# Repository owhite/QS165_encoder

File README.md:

# QS165 motor magentic encoder with hall output

One scope probe (red) connected to "W" output of board, and another probe (yellow) is tied to the phase output of the QS165. The QS165 is turned by hand as described here: 

[LINK](https://github.com/badgineer/MP2-ESC/blob/main/docs/MOTOR_PARAM.md).

## An encoder retrofit for the QS165 motor [[See this link](AS5048_extburn/README.md)].

This encoder is designed as a drop in replacement to the QS165 motor and uses an AS5047 to generates UVW output. In order for this to work you'll need to program the AS5047 with an external CPU. So basically this is **unnecessarily expensive requiring purchase of a custum PCB and a teensy to program the board. It is unnecessarily complicated in that it requires a custom programmer dongle, common bench testing equipment, assembling a board, and knowledge of programming**. 

On the other hand I'm not aware of a lot of alternatives. 

### **Acknowledgement:**
* [CircularBuffer](https://github.com/CircularBuffer/AS5047P) supplied code to burn the AS5047 non-volatile memory.
* [David Molony](https://github.com/davidmolony) kindly helped with some development of early boards. 

## Schematic

## To build board and test
* Order and construct [this kicad board](AS5047_extburn/README.md)
* Create the programming dongle shown below
* Select between 3.3V versus 5V operation with solder jumper
* Please note: using 5V on the 3.3V definitely kills the chip
* Connect up up the finished PCB on the bench or motor
* Confirm the initial outputs of the AS5047 with an oscilloscope

## Programming
The AS5047 uses one time progromming to change some of it's registers permanantly. Note that programming definitely means you get **one time** to program the chip -- so be careful. 

As [CircularBuffer](https://github.com/CircularBuffer/AS5047P) points out, that code will probably work on a number of platforms. This works for me:

* Review [main.ino](https://github.com/owhite/QS165_encoder/tree/main/FIRMWARE/encoder/src/main.ino) carefully to understand how variables are sent to the AS5047 and the program flow
* Default variables for QS165 are set in main.ino using the lines:

```
  AS5047P_SetFieldInRegister(&encInstanceA, AS5047P_SETTINGS1, AS5047P_SETTINGS1_PWMON, 1);
  AS5047P_SetFieldInRegister(&encInstanceA, AS5047P_SETTINGS1, AS5047P_SETTINGS1_UVW_ABI, 1);
  AS5047P_SetFieldInRegister(&encInstanceA, AS5047P_SETTINGS2, AS5047P_SETTINGS2_UVWPP, 6);
```

Note: the QS165 has 7 polepairs, and according to the AS5047 docs you pass it a '6'. 

* Salt to taste if you have something else
* Load code on teensy board using the platformio environment to install [code](https://github.com/owhite/QS165_encoder/tree/main/FIRMWARE/encoder)
* Once programmed, connect teensy to encoder board using programming-dongle
* Start up a serial terminal
* While program is running, review the program is effectively communicating with the encoder board
* Confirm you like the actual output of the pins on encoder board
* Entering single characters into the serial input gets ready for the burn
* Typing anything besides "x" shows you serial input is working
* Enter "x" when youre ready to burn
* main.ino will report "no errors received, test if burn complete" if it worked
* Once it is programmed, youre done, and the AS5047 will not let you burn again.

## Programming hardware

An example of programming a earlier version of the encoder board with a teensy 3.6, ribbon cable and 6 pin connector. 

Pogo pins may be helpful for making quick connections to the board. 

## Shout out to my friends:
* Need a nice open source motor controller? Try the [MP2](https://github.com/badgineer/MP2-ESC). 
* Need some firmware to run on the motor controller? Try [MESC](https://github.com/davidmolony/MESC_Firmware). 
* A discussion of the QS165 on [endless-sphere](https://endless-sphere.com/forums/viewtopic.php?p=1748544).
* Two great sites for PCB and PCBA: [pcbway.com](https://www.pcbway.com/) and [jlcpcb.com](https://jlcpcb.com/).

## Final notes: some examples of other attempts to create an encoder
### **Attempt: AS5048 with line isolation [[LINK](AS5048_isolation/README.md)].**

Note: was not bad, just sort of complicated to use SPI with ESC.

### **Attempt: atmega328p to AS5048 [[LINK](AS5048_atmega328p/README.md)].**

Notes: Never really got this to work. 
* decoupling caps werent doing their job on original design which could be the cause;
* original xtal just didnt work;
* this may have resulted in serial writing bad characters;
* and programming problems. 

And, it's not clear the clock speed would ever be fast enough for SPI communications and reasonable output

PCB was set up for 5v. 

### **Attempt: AS5047 with on board CPU [[LINK](AS5047_atmega328p/README.md)].** 
This actually generated some reasonable output, but the downside it required the atmega to push SPI instructions to the AS5047.

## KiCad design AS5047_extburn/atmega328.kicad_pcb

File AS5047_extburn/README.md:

# An encoder retrofit for the QS165 motor.

Review this [README](../README.md) for more information.

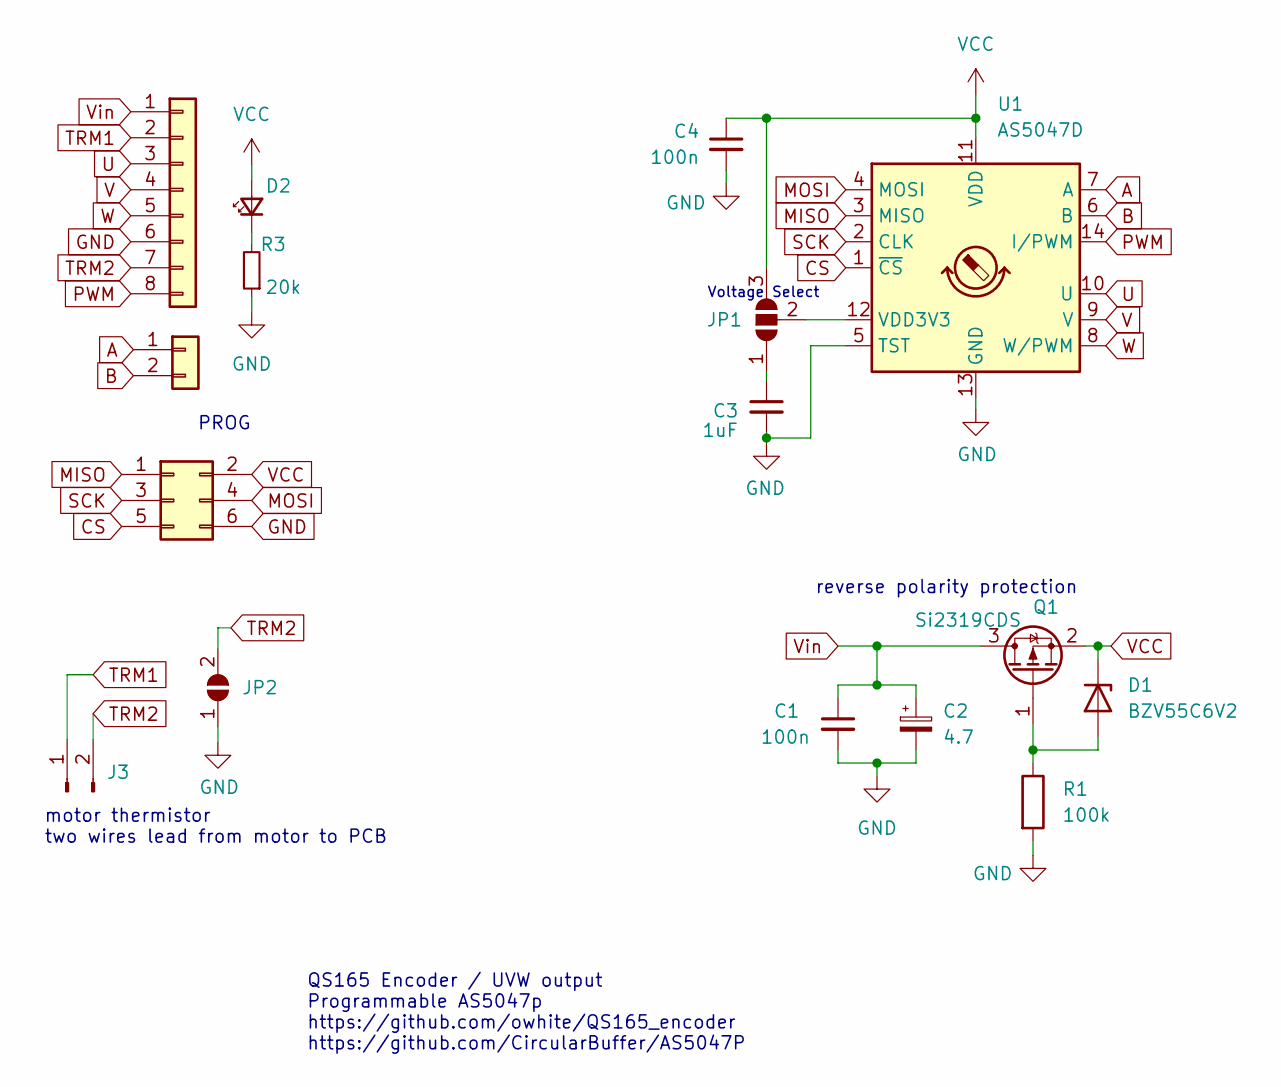
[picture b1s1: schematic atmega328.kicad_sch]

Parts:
C1, C4: 100n; C_0805_2012Metric
C2: 4.7; CP_EIA-3216-18_Kemet-A; LCSC C110055
C3: 1uF; C_0805_2012Metric
D1: BZV55C6V2; D_MiniMELF; LCSC C266263
D2: RED_LED; LED_0805_2012Metric
J1: Conn_01x02; PinHeader_1x02_P2.54mm_Vertical
J3: Conn_01x02_Male; PinHeader_1x02_P2.54mm_Vertical
J5: Conn_01x08; PinHeader_1x08_P2.54mm_Vertical
JP1: SolderJumper_3_Open; SolderJumper-3_P1.3mm_Open_RoundedPad1.0x1.5mm
JP2: SolderJumper_2_Open; SolderJumper-2_P1.3mm_Open_Pad1.0x1.5mm
PRG1: Conn_02x03_Top_Bottom; isp_6pin
Q1: Si2319CDS; SOT-23; LCSC C558254
R1: 100k; R_0805_2012Metric
R3: 20k; R_0805_2012Metric
U1: AS5047D; TSSOP-14_4.4x5mm_P0.65mm

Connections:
A: J1.1, U1.7 (A)
B: J1.2, U1.6 (B)
CS: PRG1.5, U1.1 (~CS)
GND: C1.2, C2.2, C3.2, C4.2, J5.6, JP2.1 (A), PRG1.6, R1.2, R3.1, U1.5 (TST), U1.13 (GND)
MISO: PRG1.1, U1.3 (MISO)
MOSI: PRG1.4, U1.4 (MOSI)
unnamed: C3.1, JP1.1 (A)
unnamed: D1.2 (A), Q1.1 (G), R1.1
unnamed: D2.1 (K), R3.2
unnamed: JP1.2 (C), U1.12 (VDD3V3)
PWM: J5.8, U1.14 (I/PWM)
SCK: PRG1.3, U1.2 (CLK)
TRM1: J3.1, J5.2
TRM2: J3.2, J5.7, JP2.2 (B)
U: J5.3, U1.10 (U)
V: J5.4, U1.9 (V)
VCC: C4.1, D1.1 (K), D2.2 (A), JP1.3 (B), PRG1.2, Q1.2 (S), U1.11 (VDD)
Vin: C1.1, C2.1, J5.1, Q1.3 (D)
W: J5.5, U1.8 (W/PWM)

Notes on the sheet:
QS165 Encoder / UVW output Programmable AS5047p https://github.com/owhite/QS165_encoder https://github.com/CircularBuffer/AS5047P
motor thermistor two wires lead from motor to PCB
PROG
reverse polarity protection
Voltage Select

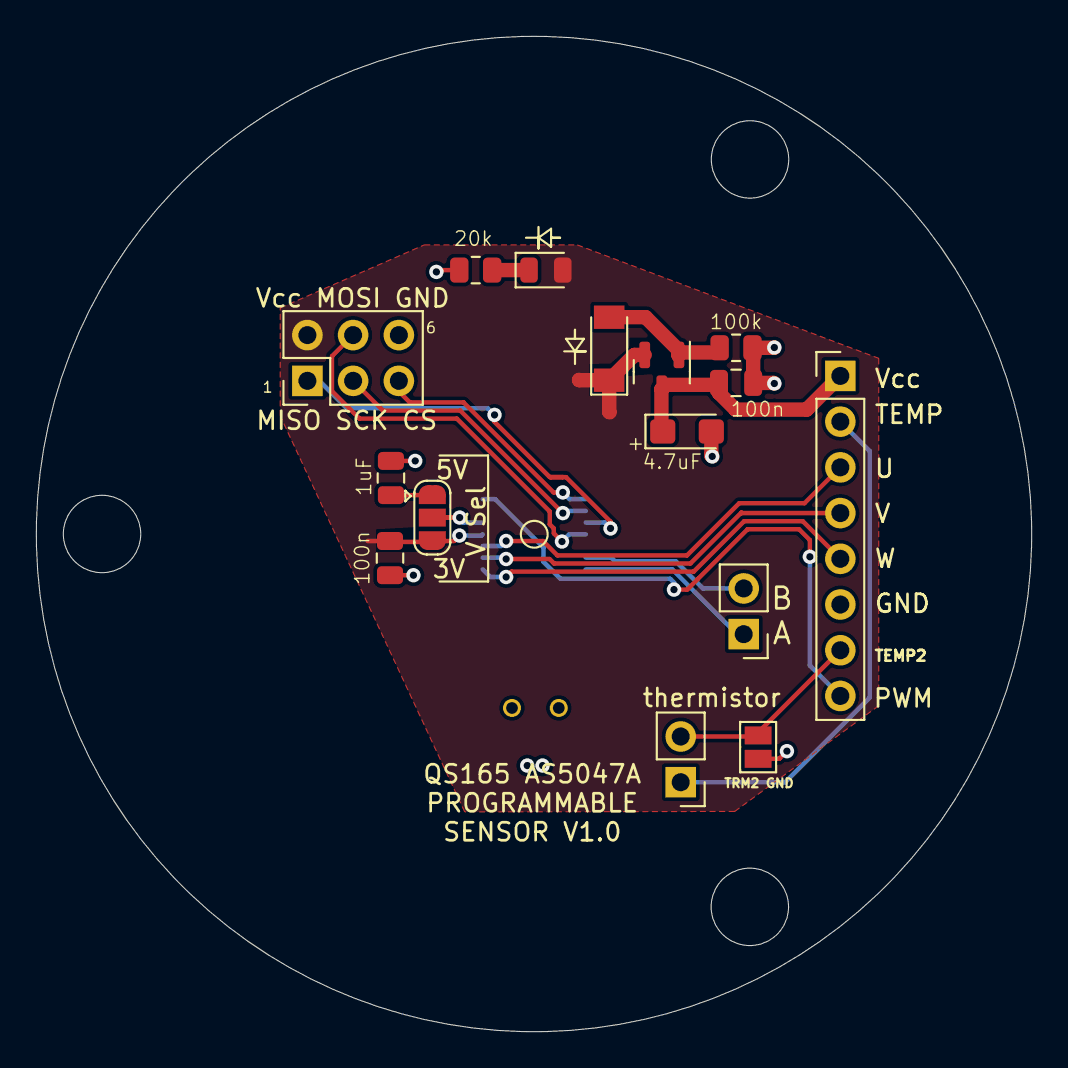
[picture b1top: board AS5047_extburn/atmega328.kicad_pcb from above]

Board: 2 copper layers, 55.3 x 55.3 mm, 16 parts (1 on the bottom side), 19 nets.

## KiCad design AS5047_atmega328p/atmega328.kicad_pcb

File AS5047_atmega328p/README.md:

# Native AS5047 hall output, driven by atmega328p

See the firmware directory to run the atmega.

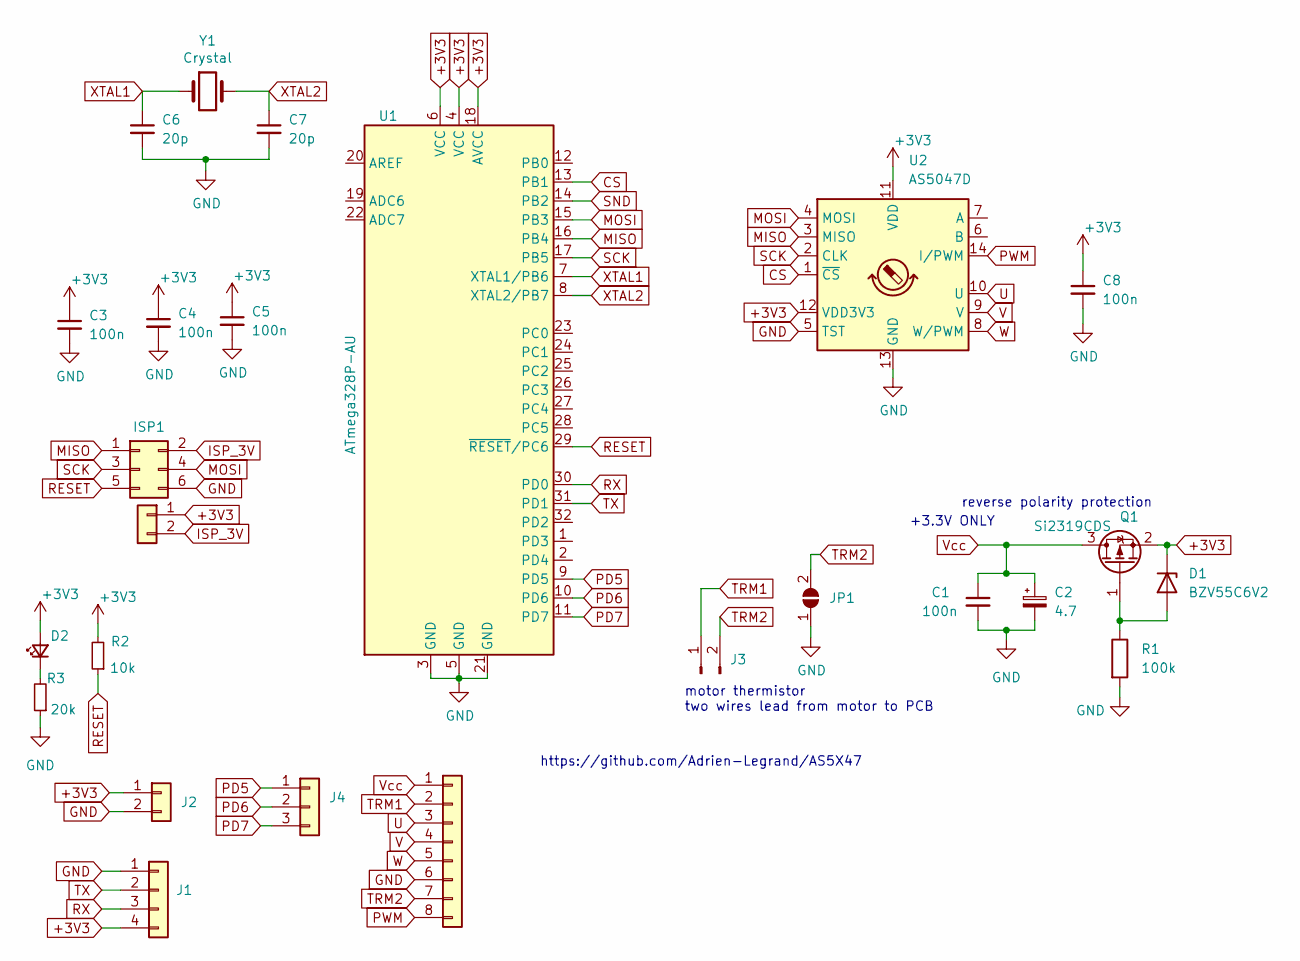
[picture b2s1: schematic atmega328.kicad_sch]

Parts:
C1: 100n; C_0603_1608Metric; LCSC C346191
C2: 4.7; CP_EIA-3216-18_Kemet-A; LCSC C110055
C3, C4, C5, C8: 100n; C_0402_1005Metric; LCSC C1525
C6, C7: 20p; C_0402_1005Metric; LCSC C76959
D1: BZV55C6V2; D_MiniMELF; LCSC C266263
D2: RED_LED; LED_0603_1608Metric; LCSC C90692
ISP1: Conn_02x03_Top_Bottom; isp_6pin
J1: Conn_01x04; PinHeader_1x04_P2.54mm_Vertical
J2: Conn_01x02; myPinHeader_1x02_P2.54mm_Vertical
J3: Conn_01x02_Male; PinHeader_1x02_P2.54mm_Vertical
J4: Conn_01x03; PinHeader_1x03_P2.54mm_Vertical
J5: Conn_01x08; PinHeader_1x08_P2.54mm_Vertical
J6: Conn_01x02; PinHeader_1x02_P2.54mm_Vertical
JP1: SolderJumper_2_Open; SolderJumper-2_P1.3mm_Open_Pad1.0x1.5mm
Q1: Si2319CDS; SOT-23; LCSC C558254
R1: 100k; R_0603_1608Metric; LCSC C14675
R2: 10k; R_0603_1608Metric; LCSC C98220
R3: 20k; R_0603_1608Metric; LCSC C365403
U1: ATmega328P-AU; TQFP-32_7x7mm_P0.8mm; LCSC C14877
U2: AS5047D; TSSOP-14_4.4x5mm_P0.65mm
Y1: Crystal; Crystal_SMD_5032-2Pin_5.0x3.2mm

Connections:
+3V3: C3.1, C4.1, C5.1, C8.1, D1.1 (K), D2.2 (A), J1.4, J2.1, J6.1, Q1.2 (S), R2.2, U1.4 (VCC), U1.6 (VCC), U1.18 (AVCC), U2.11 (VDD), U2.12 (VDD3V3)
CS: U1.13 (PB1), U2.1 (~CS)
GND: C1.2, C2.2, C3.2, C4.2, C5.2, C6.2, C7.2, C8.2, ISP1.6, J1.1, J2.2, J5.6, JP1.1 (A), R1.2, R3.1, U1.3 (GND), U1.5 (GND), U1.21 (GND), U2.5 (TST), U2.13 (GND)
ISP_3V: ISP1.2, J6.2
MISO: ISP1.1, U1.16 (PB4), U2.3 (MISO)
MOSI: ISP1.4, U1.15 (PB3), U2.4 (MOSI)
unnamed: D1.2 (A), Q1.1 (G), R1.1
unnamed: D2.1 (K), R3.2
PD5: J4.1, U1.9 (PD5)
PD6: J4.2, U1.10 (PD6)
PD7: J4.3, U1.11 (PD7)
PWM: J5.8, U2.14 (I/PWM)
RESET: ISP1.5, R2.1, U1.29 (~RESET/PC6)
RX: J1.3, U1.30 (PD0)
SCK: ISP1.3, U1.17 (PB5), U2.2 (CLK)
SND: U1.14 (PB2)
TRM1: J3.1, J5.2
TRM2: J3.2, J5.7, JP1.2 (B)
TX: J1.2, U1.31 (PD1)
U: J5.3, U2.10 (U)
V: J5.4, U2.9 (V)
Vcc: C1.1, C2.1, J5.1, Q1.3 (D)
W: J5.5, U2.8 (W/PWM)
XTAL1: C6.1, U1.7 (XTAL1/PB6), Y1.1
XTAL2: C7.1, U1.8 (XTAL2/PB7), Y1.2

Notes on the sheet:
+3.3V ONLY
motor thermistor two wires lead from motor to PCB
reverse polarity protection
https://github.com/Adrien-Legrand/AS5X47

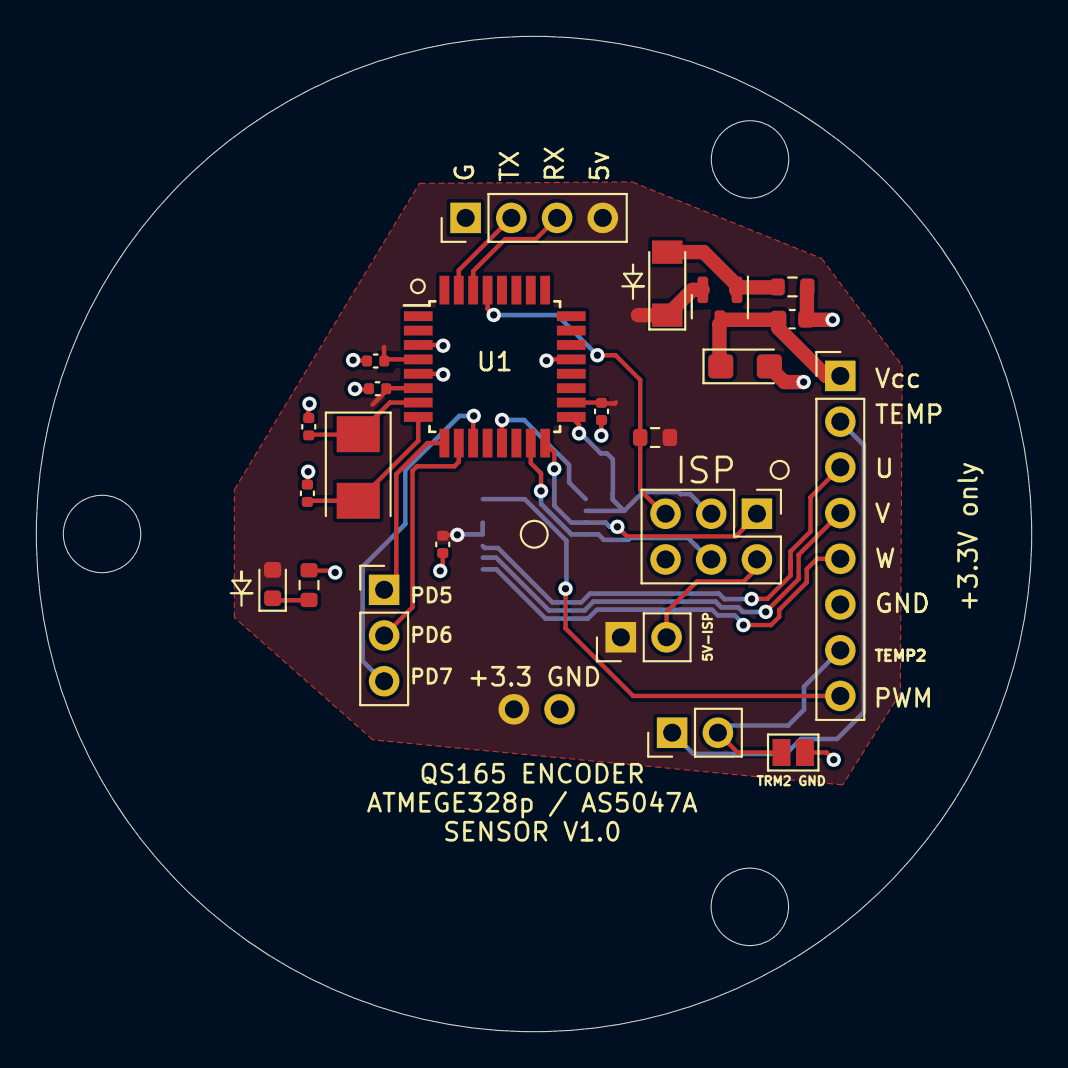
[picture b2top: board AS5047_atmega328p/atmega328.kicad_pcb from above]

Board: 2 copper layers, 55.3 x 55.3 mm, 25 parts (1 on the bottom side), 24 nets.

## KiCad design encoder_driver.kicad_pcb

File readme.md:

# QS165_encoder
QS165 encoder based on the TLE5012B encoder and galvanic isolators.

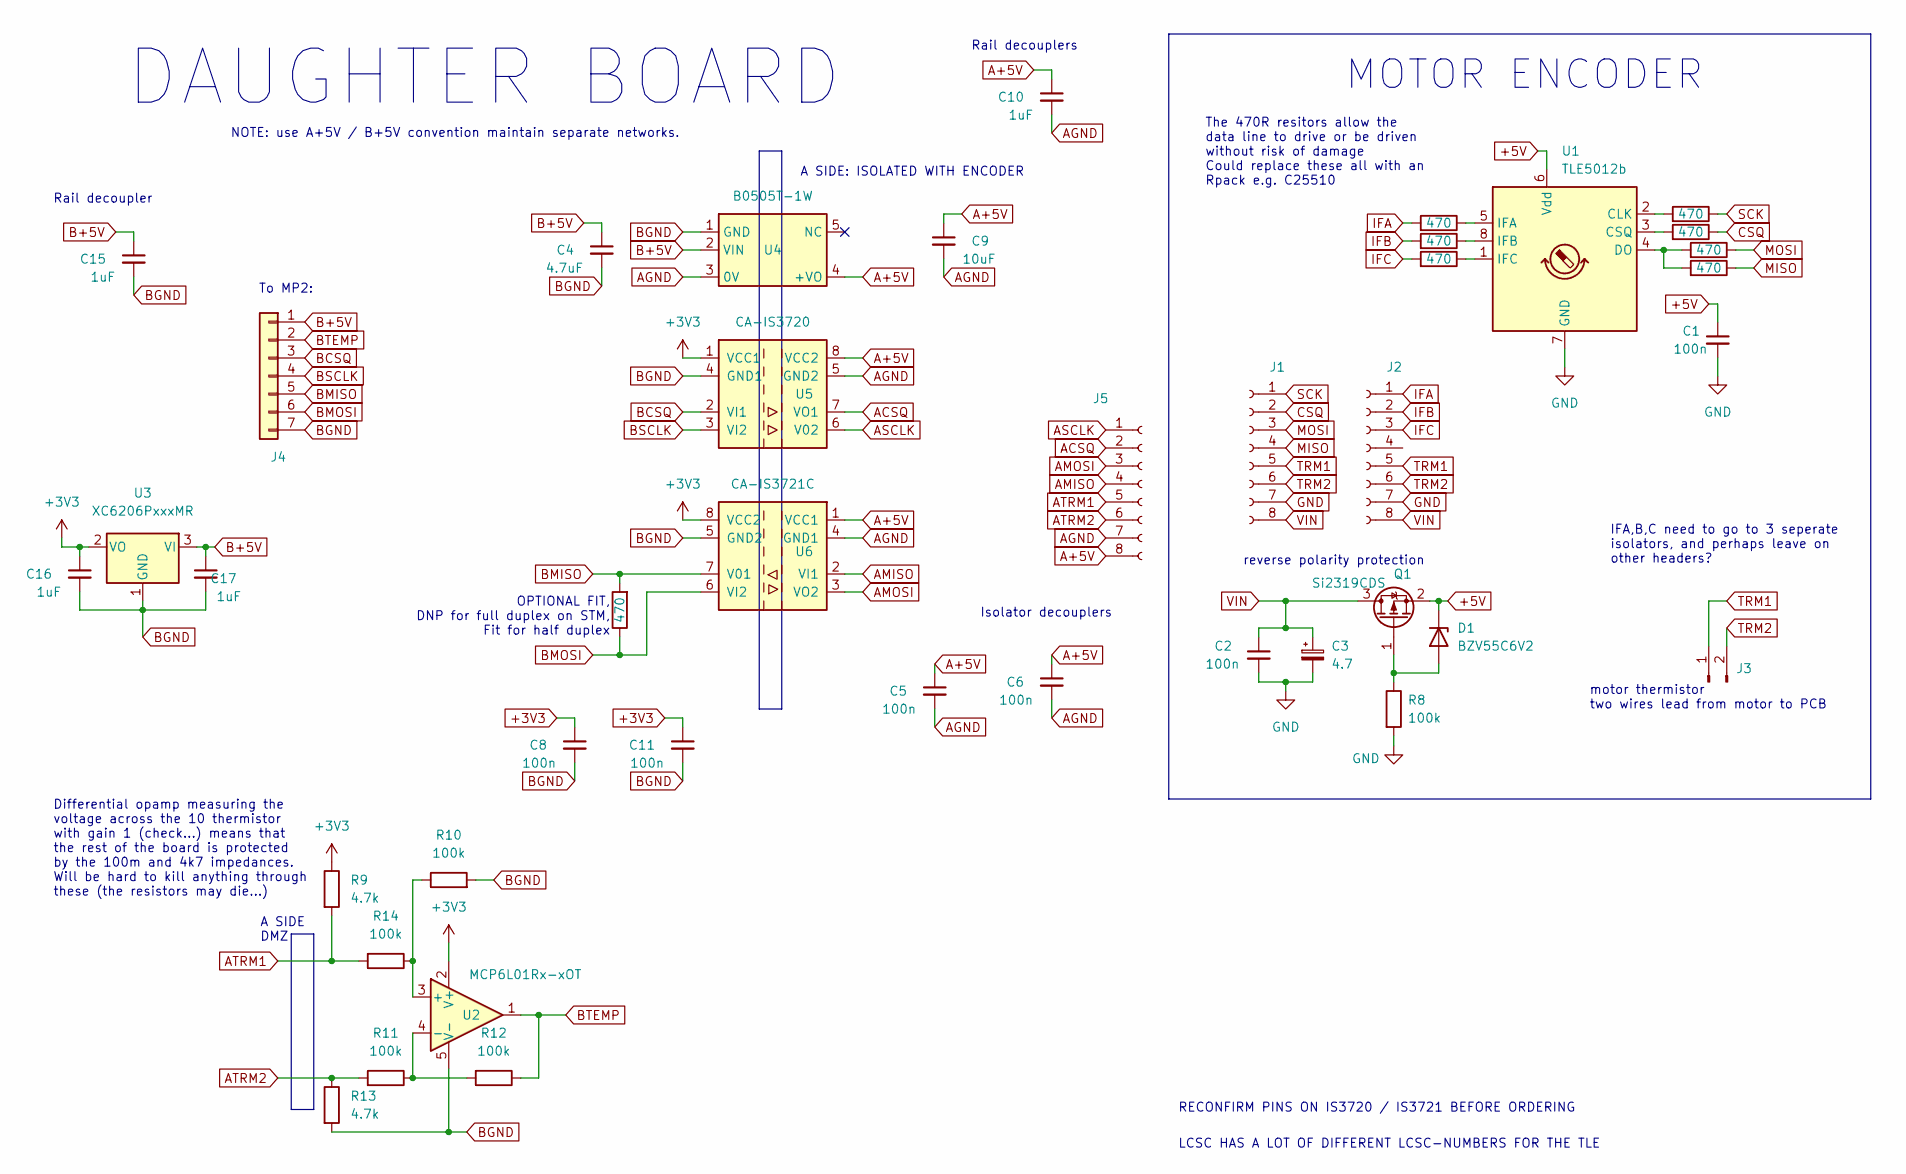
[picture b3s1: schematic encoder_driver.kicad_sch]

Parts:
C1, C2: 100n; C_0603_1608Metric; LCSC C14663
C3: 4.7; CP_EIA-3216-18_Kemet-A; LCSC C110055
C4: 4.7uF; C_0603_1608Metric; LCSC C15849
C5, C6, C8, C11: 100n; C_0402_1005Metric; LCSC C14663
C9: 10uF; C_0603_1608Metric; LCSC C15849
C10, C15, C16, C17: 1uF; C_0603_1608Metric; LCSC C15849
D1: BZV55C6V2; D_MiniMELF; LCSC C266263
J1, J2: Conn_01x08_Female; PinSocket_1x08_P2.54mm_Vertical
J3: Conn_01x02_Male; PinHeader_1x02_P2.54mm_Vertical
J4: Conn_01x07; PinSocket_1x07_P2.00mm_Vertical
J5: Conn_01x08_Female; PinHeader_1x08_P2.54mm_Vertical
Q1: Si2319CDS; SOT-23; LCSC C558254
R1, R2, R3, R4, R5, R6, R7, R15: 470; R_0603_1608Metric; LCSC C23179
R8: 100k; R_0603_1608Metric; LCSC C25803
R9, R13: 4.7k; R_0402_1005Metric; LCSC C23186
R10, R11, R12, R14: 100k; R_0402_1005Metric; LCSC C25803
U1: TLE5012b; my_Infineon_PG-DSO-8
U2: MCP6L01Rx-xOT; SOT-23-5; LCSC C693056
U3: XC6206PxxxMR; SOT-23; LCSC C5446
U4: B0505T-1W; PWRM-SMD_B0505XT-1WR2; LCSC C30338
U5: CA-IS3720; SOIC-8_3.9x4.9mm_P1.27mm; LCSC C428882
U6: CA-IS3721C; SOIC-8_3.9x4.9mm_P1.27mm; LCSC C5121216

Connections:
+3V3: C8.1, C11.1, C16.1, R9.1, U2.2 (V+), U3.2 (VO), U5.1 (VCC1), U6.8 (VCC2)
+5V: C1.1, D1.1 (K), Q1.2 (S), U1.6 (Vdd)
A+5V: C5.1, C6.1, C9.1, C10.1, J5.8, U4.4 (+VO), U5.8 (VCC2), U6.1 (VCC1)
ACSQ: J5.2, U5.7 (VO1)
AGND: C5.2, C6.2, C9.2, C10.2, J5.7, U4.3 (0V), U5.5 (GND2), U6.4 (GND1)
AMISO: J5.4, U6.2 (VI1)
AMOSI: J5.3, U6.3 (VO2)
ASCLK: J5.1, U5.6 (V02)
ATRM1: J5.5, R9.2, R14.2
ATRM2: J5.6, R11.2, R13.1
B+5V: C4.1, C15.1, C17.1, J4.1, U3.3 (VI), U4.2 (VIN)
BCSQ: J4.3, U5.2 (VI1)
BGND: C4.2, C8.2, C11.2, C15.2, C16.2, C17.2, J4.7, R10.2, R13.2, U2.5 (V-), U3.1 (GND), U4.1 (GND), U5.4 (GND1), U6.5 (GND2)
BMISO: J4.5, R15.2, U6.7 (V01)
BMOSI: J4.6, R15.1, U6.6 (VI2)
BSCLK: J4.4, U5.3 (VI2)
BTEMP: J4.2, R12.1, U2.1
CSQ: J1.2, R5.1
GND: C1.2, C2.2, C3.2, J1.7, J2.7, R8.2, U1.7 (GND)
IFA: J2.1, R1.2
IFB: J2.2, R2.2
IFC: J2.3, R3.2
MISO: J1.4, R7.1
MOSI: J1.3, R6.1
unnamed: D1.2 (A), Q1.1 (G), R8.1
unnamed: R1.1, U1.5 (IFA)
unnamed: R2.1, U1.8 (IFB)
unnamed: R3.1, U1.1 (IFC)
unnamed: R4.2, U1.2 (CLK)
unnamed: R5.2, U1.3 (CSQ)
unnamed: R6.2, R7.2, U1.4 (DO)
unnamed: R10.1, R14.1, U2.3 (+)
unnamed: R11.1, R12.2, U2.4 (-)
SCK: J1.1, R4.1
TRM1: J1.5, J2.5, J3.1
TRM2: J1.6, J2.6, J3.2
VIN: C2.1, C3.1, J1.8, J2.8, Q1.3 (D)

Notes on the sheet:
MOTOR ENCODER
motor thermistor two wires lead from motor to PCB
Rail decoupler
Differential opamp measuring the voltage across the 10 thermistor with gain 1 (check...) means that the rest of the board is protected by the 100m and 4k7 impedances. Will be hard to kill anything through these (the resistors may die...)
reverse polarity protection
To MP2:
A SIDE DMZ
Rail decouplers
OPTIONAL FIT, DNP for full duplex on STM, Fit for half duplex
LCSC HAS A LOT OF DIFFERENT LCSC-NUMBERS FOR THE TLE
DAUGHTER BOARD
IFA,B,C need to go to 3 seperate isolators, and perhaps leave on other headers?
NOTE: use A+5V / B+5V convention maintain separate networks.
Isolator decouplers
RECONFIRM PINS ON IS3720 / IS3721 BEFORE ORDERING
A SIDE: ISOLATED WITH ENCODER
The 470R resitors allow the data line to drive or be driven without risk of damage Could replace these all with an Rpack e.g. C25510

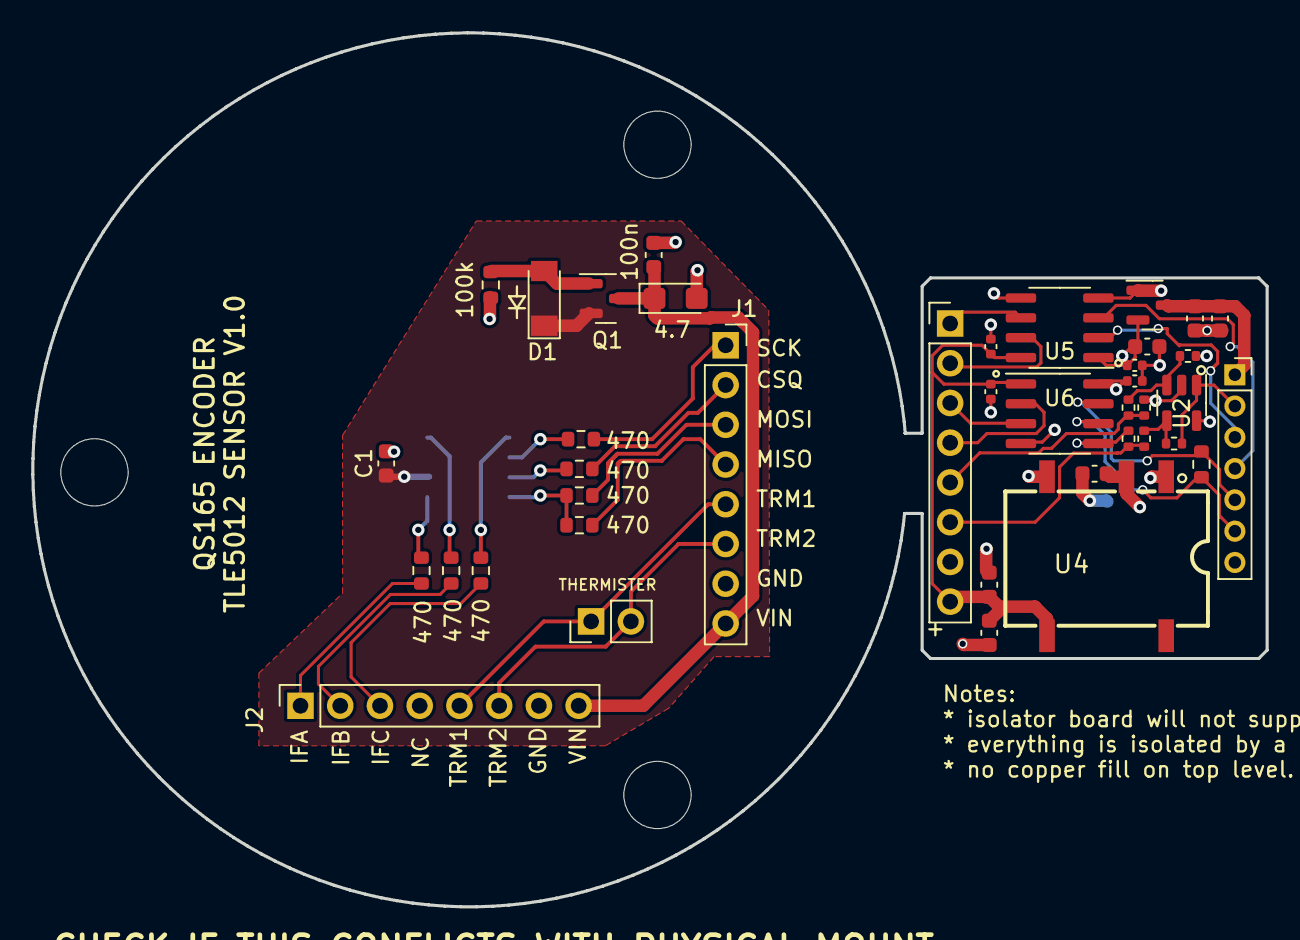
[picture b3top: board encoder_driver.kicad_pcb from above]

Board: 4 copper layers, 78.9 x 55.9 mm, 41 parts (1 on the bottom side), 37 nets.

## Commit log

2022-10-11 initiate project
2022-10-11 edit schematic
2022-11-02 lots of layout
2022-11-02 added pic
2022-11-02 added outline
2022-11-03 edits
2022-11-03 GERBERS
2022-11-17 things
2022-11-17 TLE5012 encoder initialization
2022-11-18 added isolators
2022-11-19 DMM Add opamp based thermistor measurement prototype Half duplex SPI option for encoder 3v3 for output to F405 board (does not like 5V on some inputs) Some component assignments to LCSC numbers
2022-11-22 near final draft
2022-11-22 submitted to jlcpcb
2022-12-05 error with U2
2022-12-20 created new version
2022-12-20 created V1.1
2023-01-06 recreating lost AS5048 version
2023-01-07 JCLPCB V1.2 order
2023-01-07 added firmware
2023-01-08 new notes
2023-01-22 new documentation
2023-01-26 test
2023-02-06 edited README
